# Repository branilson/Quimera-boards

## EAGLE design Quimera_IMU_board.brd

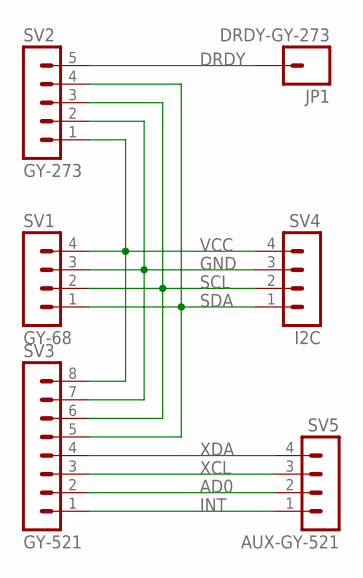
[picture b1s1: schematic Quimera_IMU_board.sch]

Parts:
JP1: DRDY-GY-273; 1X01_OFFSET
SV1: GY-68; MA04-1
SV2: GY-273; MA05-1
SV3: GY-521; MA08-1
SV4: I2C; MA04-1
SV5: AUX-GY-521; MA04-1

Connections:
AD0: SV3.2, SV5.2
DRDY: JP1.1, SV2.5
GND: SV1.3, SV2.2, SV3.7, SV4.3
INT: SV3.1, SV5.1
SCL: SV1.2, SV2.3, SV3.6, SV4.2
SDA: SV1.1, SV2.4, SV3.5, SV4.1
VCC: SV1.4, SV2.1, SV3.8, SV4.4
XCL: SV3.3, SV5.3
XDA: SV3.4, SV5.4

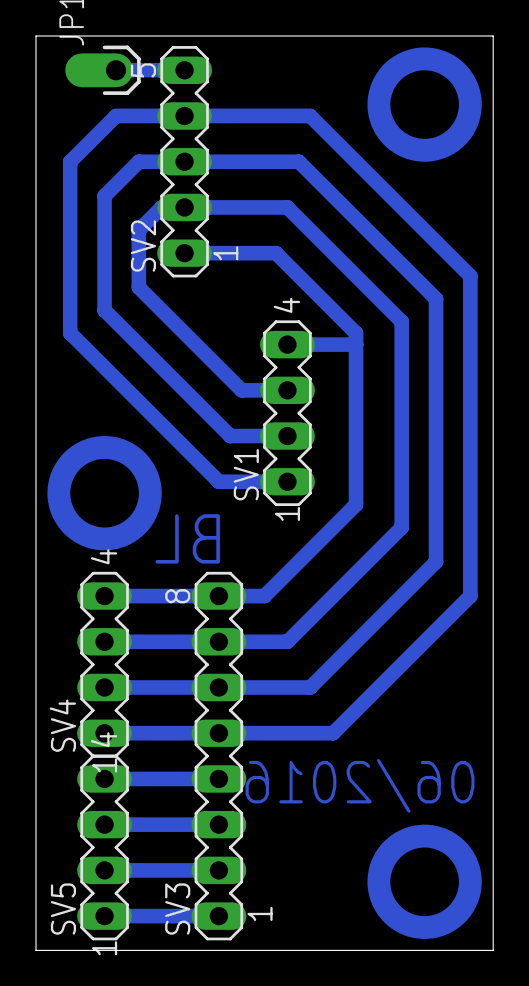
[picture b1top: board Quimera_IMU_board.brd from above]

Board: 2 copper layers, 25.4 x 50.8 mm, 6 parts (0 on the bottom side), 9 nets.

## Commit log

2018-02-22 Old boards designs used on Quimera robot

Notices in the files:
parts and their libraries:
SparkFun-Connectors: Licensing: Creative Commons ShareAlike 4.0 International - https://creativecommons.org/licenses/by-sa/4.0
